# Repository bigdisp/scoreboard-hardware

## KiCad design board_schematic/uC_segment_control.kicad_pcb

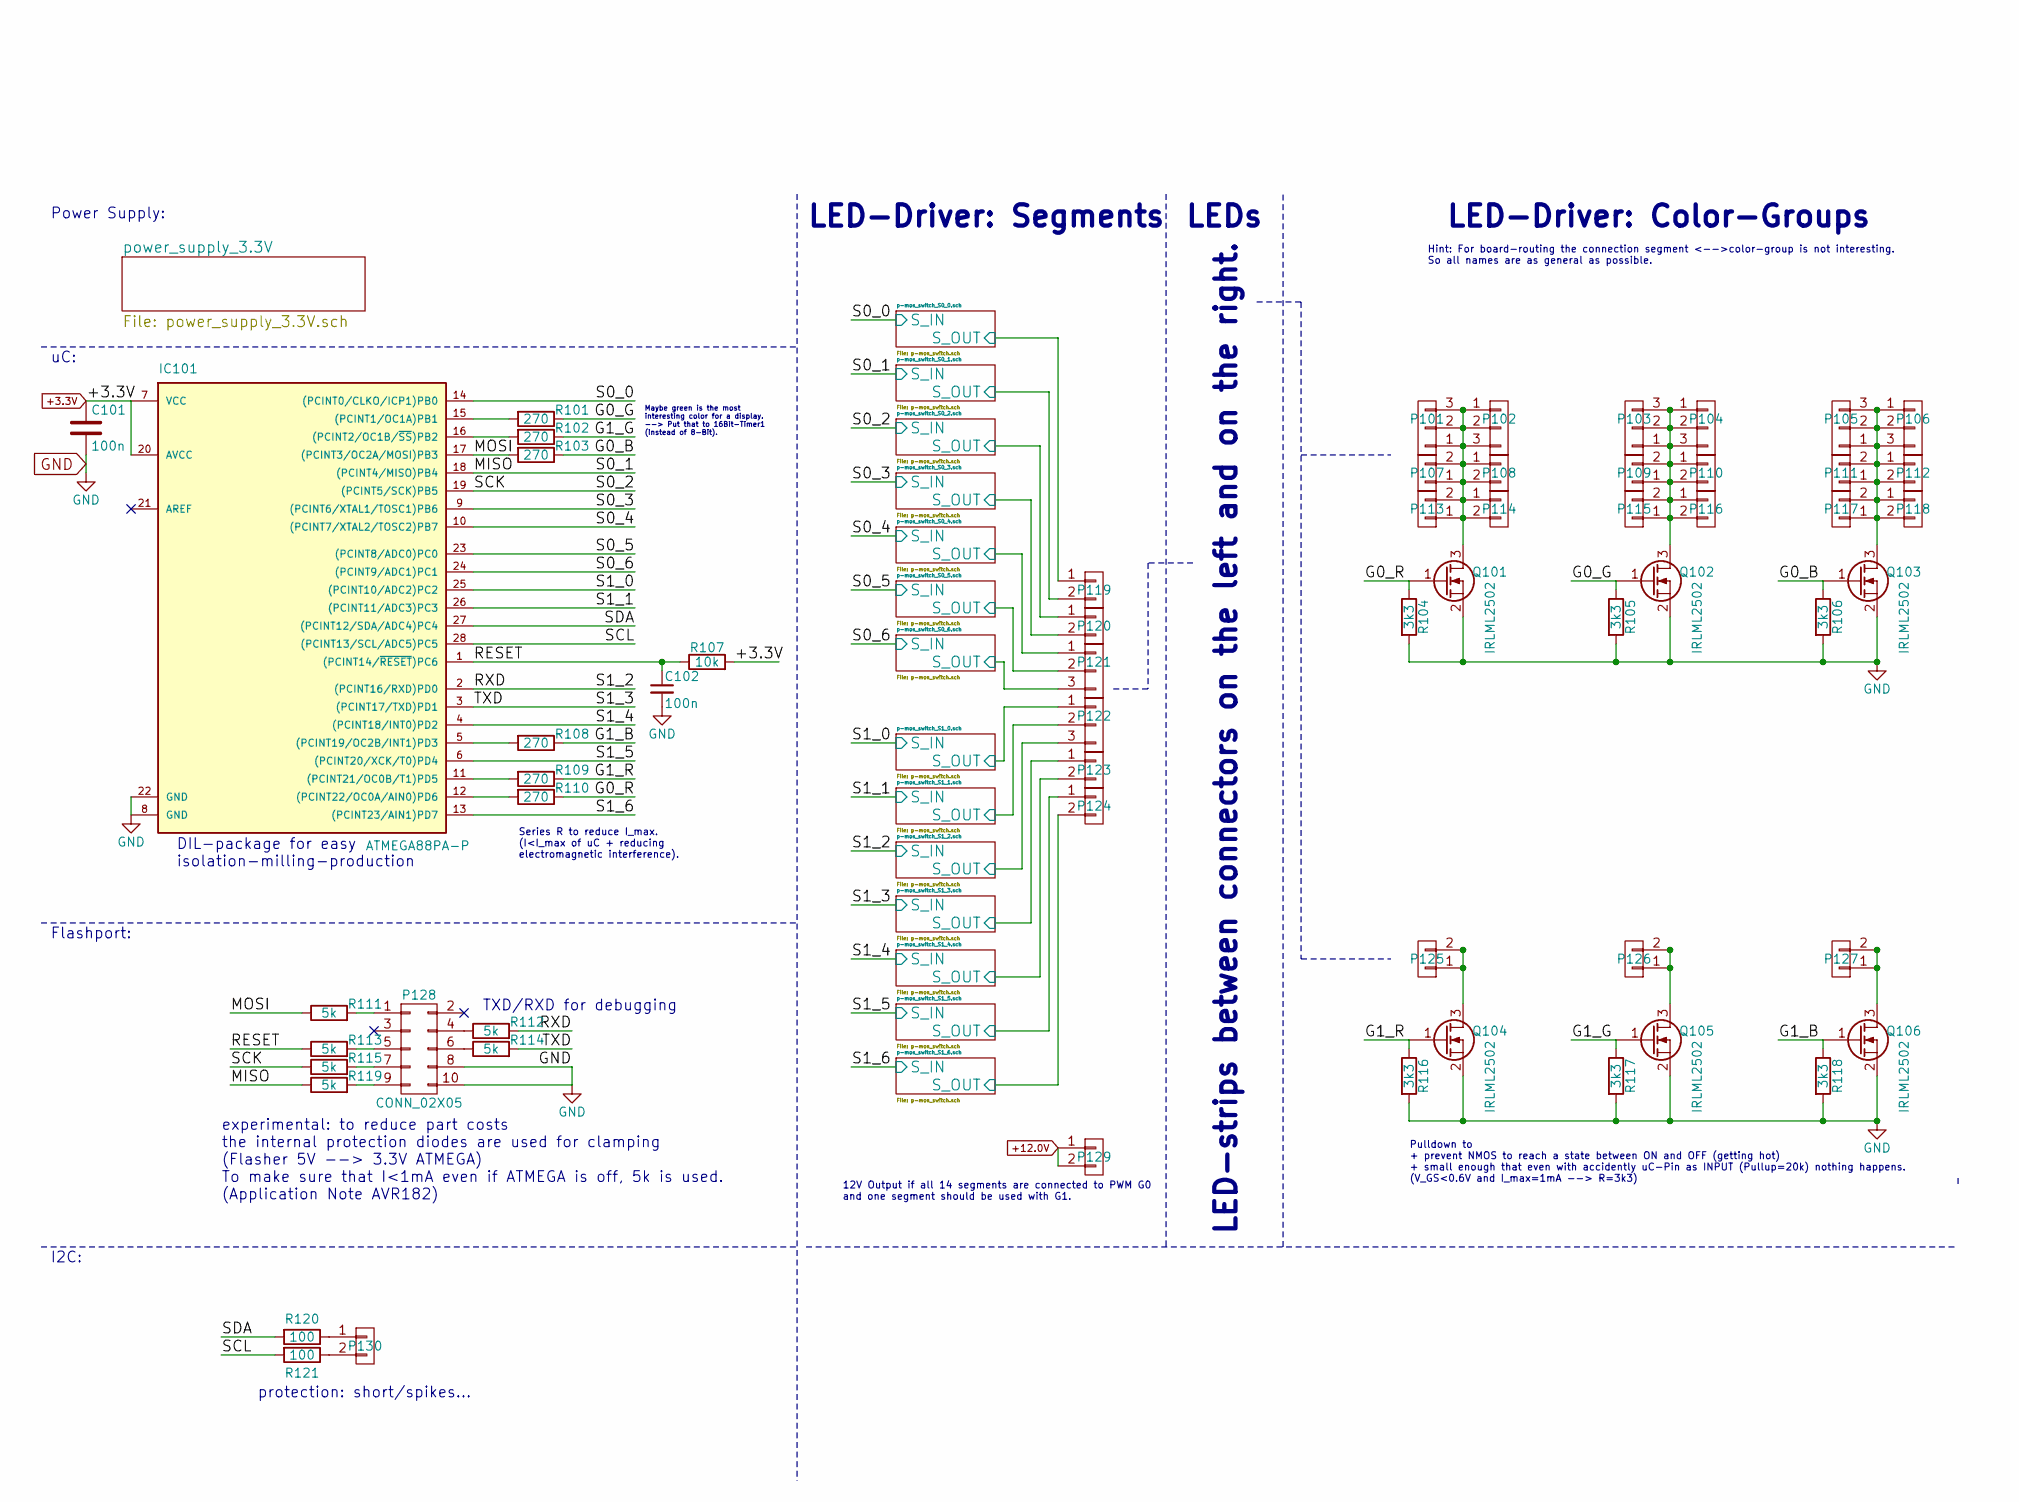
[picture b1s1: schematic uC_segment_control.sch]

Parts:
C101, C102: 100n; C_0805_HandSoldering
IC101: ATMEGA88PA-P; DIP-28_W7.62mm_LongPads
P101, P102, P103, P104, P105, P106, P121, P122: CONN_01X03; AK300-3
P107, P108, P109, P110, P111, P112, P113, P114, P115, P116, P117, P118, P119, P120, P123, P124, P125, P126, P127, P129, P130: CONN_01X02; AK300-2
P128: CONN_02X05; IDC_Header_Straight_10pins_0.6_clearance
Q101, Q102, Q103, Q104, Q105, Q106: IRLML2502; SOT-23_Handsoldering
R101, R102, R103, R108, R109, R110: 270; R_0805_HandSoldering
R104, R105, R106, R116, R117, R118: 3k3; R_0805_HandSoldering
R107: 10k; R_0805_HandSoldering
R111, R112, R113, R114, R115, R119: 5k; R_0805_HandSoldering
R120, R121: 100; R_0805_HandSoldering

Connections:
+3.3V: C101.1, IC101.7 (VCC), IC101.20 (AVCC), R107.2; also elsewhere on the board
+12.0V: P129.1, P129.2; also elsewhere on the board
/G0_B: Q103.1 (G), R103.1, R106.1
/G0_G: Q102.1 (G), R101.1, R105.1
/G0_R: Q101.1 (G), R104.1, R110.1
/G1_B: Q106.1 (G), R108.1, R118.1
/G1_G: Q105.1 (G), R102.1, R117.1
/G1_R: Q104.1 (G), R109.1, R116.1
/MOSI: IC101.17 ((PCINT3/OC2A/MOSI)PB3), R103.2, R111.1
/RESET: C102.1, IC101.1 ((PCINT14/~RESET~)PC6), R107.1, R113.1
/SCL: IC101.28 ((PCINT13/SCL/ADC5)PC5), R121.2
/SDA: IC101.27 ((PCINT12/SDA/ADC4)PC4), R120.2
/p-mos_switch_S0_0.sch/S_IN: IC101.14 ((PCINT0/CLKO/ICP1)PB0); also elsewhere on the board
/p-mos_switch_S0_0.sch/S_OUT: P119.1; also elsewhere on the board
/p-mos_switch_S0_1.sch/S_IN: IC101.18 ((PCINT4/MISO)PB4), R119.1; also elsewhere on the board
/p-mos_switch_S0_1.sch/S_OUT: P119.2; also elsewhere on the board
/p-mos_switch_S0_2.sch/S_IN: IC101.19 ((PCINT5/SCK)PB5), R115.1; also elsewhere on the board
/p-mos_switch_S0_2.sch/S_OUT: P120.1; also elsewhere on the board
/p-mos_switch_S0_3.sch/S_IN: IC101.9 ((PCINT6/XTAL1/TOSC1)PB6); also elsewhere on the board
/p-mos_switch_S0_3.sch/S_OUT: P120.2; also elsewhere on the board
/p-mos_switch_S0_4.sch/S_IN: IC101.10 ((PCINT7/XTAL2/TOSC2)PB7); also elsewhere on the board
/p-mos_switch_S0_4.sch/S_OUT: P121.1; also elsewhere on the board
/p-mos_switch_S0_5.sch/S_IN: IC101.23 ((PCINT8/ADC0)PC0); also elsewhere on the board
/p-mos_switch_S0_5.sch/S_OUT: P121.2; also elsewhere on the board
/p-mos_switch_S0_6.sch/S_IN: IC101.24 ((PCINT9/ADC1)PC1); also elsewhere on the board
/p-mos_switch_S0_6.sch/S_OUT: P121.3; also elsewhere on the board
/p-mos_switch_S1_0.sch/S_IN: IC101.25 ((PCINT10/ADC2)PC2); also elsewhere on the board
/p-mos_switch_S1_0.sch/S_OUT: P122.1; also elsewhere on the board
/p-mos_switch_S1_1.sch/S_IN: IC101.26 ((PCINT11/ADC3)PC3); also elsewhere on the board
/p-mos_switch_S1_1.sch/S_OUT: P122.2; also elsewhere on the board
/p-mos_switch_S1_2.sch/S_IN: IC101.2 ((PCINT16/RXD)PD0), R112.2; also elsewhere on the board
/p-mos_switch_S1_2.sch/S_OUT: P122.3; also elsewhere on the board
/p-mos_switch_S1_3.sch/S_IN: IC101.3 ((PCINT17/TXD)PD1), R114.2; also elsewhere on the board
/p-mos_switch_S1_3.sch/S_OUT: P123.1; also elsewhere on the board
/p-mos_switch_S1_4.sch/S_IN: IC101.4 ((PCINT18/INT0)PD2); also elsewhere on the board
/p-mos_switch_S1_4.sch/S_OUT: P123.2; also elsewhere on the board
/p-mos_switch_S1_5.sch/S_IN: IC101.6 ((PCINT20/XCK/T0)PD4); also elsewhere on the board
/p-mos_switch_S1_5.sch/S_OUT: P124.1; also elsewhere on the board
/p-mos_switch_S1_6.sch/S_IN: IC101.13 ((PCINT23/AIN1)PD7); also elsewhere on the board
/p-mos_switch_S1_6.sch/S_OUT: P124.2; also elsewhere on the board
GND: C101.2, C102.2, IC101.8 (GND), IC101.22 (GND), P128.8, P128.10, Q101.2 (S), Q102.2 (S), Q103.2 (S), Q104.2 (S), Q105.2 (S), Q106.2 (S), R104.2, R105.2, R106.2, R116.2, R117.2, R118.2; also elsewhere on the board
unnamed: IC101.5 ((PCINT19/OC2B/INT1)PD3), R108.2
unnamed: IC101.11 ((PCINT21/OC0B/T1)PD5), R109.2
unnamed: IC101.12 ((PCINT22/OC0A/AIN0)PD6), R110.2
unnamed: IC101.15 ((PCINT1/OC1A)PB1), R101.2
unnamed: IC101.16 ((PCINT2/OC1B/~SS~)PB2), R102.2
unnamed: P101.1, P101.2, P101.3, P102.1, P102.2, P102.3, P107.1, P107.2, P108.1, P108.2, P113.1, P113.2, P114.1, P114.2, Q101.3 (D)
unnamed: P103.1, P103.2, P103.3, P104.1, P104.2, P104.3, P109.1, P109.2, P110.1, P110.2, P115.1, P115.2, P116.1, P116.2, Q102.3 (D)
unnamed: P105.1, P105.2, P105.3, P106.1, P106.2, P106.3, P111.1, P111.2, P112.1, P112.2, P117.1, P117.2, P118.1, P118.2, Q103.3 (D)
unnamed: P125.1, P125.2, Q104.3 (D)
unnamed: P126.1, P126.2, Q105.3 (D)
unnamed: P127.1, P127.2, Q106.3 (D)
unnamed: P128.1, R111.2
unnamed: P128.4, R112.1
unnamed: P128.5, R113.2
unnamed: P128.6, R114.1
unnamed: P128.7, R115.2
unnamed: P128.9, R119.2
unnamed: P130.1, R120.1
unnamed: P130.2, R121.1

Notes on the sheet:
DIL-package for easy isolation-milling-production
experimental: to reduce part costs the internal protection diodes are used for clamping (Flasher 5V --> 3.3V ATMEGA) To make sure that I<1mA even if ATMEGA is off, 5k is used. (Application Note AVR182)
Power Supply:
uC:
Flashport:
LED-Driver: Segments
LED-Driver: Color-Groups
Hint: For board-routing the connection segment <-->color-group is not interesting. So all names are as general as possible.
LED-strips between connectors on the left and on the right.
LEDs
Series R to reduce I_max. (I<I_max of uC + reducing electromagnetic interference).
Maybe green is the most interesting color for a display. --> Put that to 16Bit-Timer1 (instead of 8-Bit).
Pulldown to + prevent NMOS to reach a state between ON and OFF (getting hot) + small enough that even with accidently uC-Pin as INPUT (Pullup=20k) nothing happens. (V_GS<0.6V and I_max=1mA --> R=3k3)
TXD/RXD for debugging
I2C:
protection: short/spikes...
12V Output if all 14 segments are connected to PWM G0 and one segment should be used with G1.

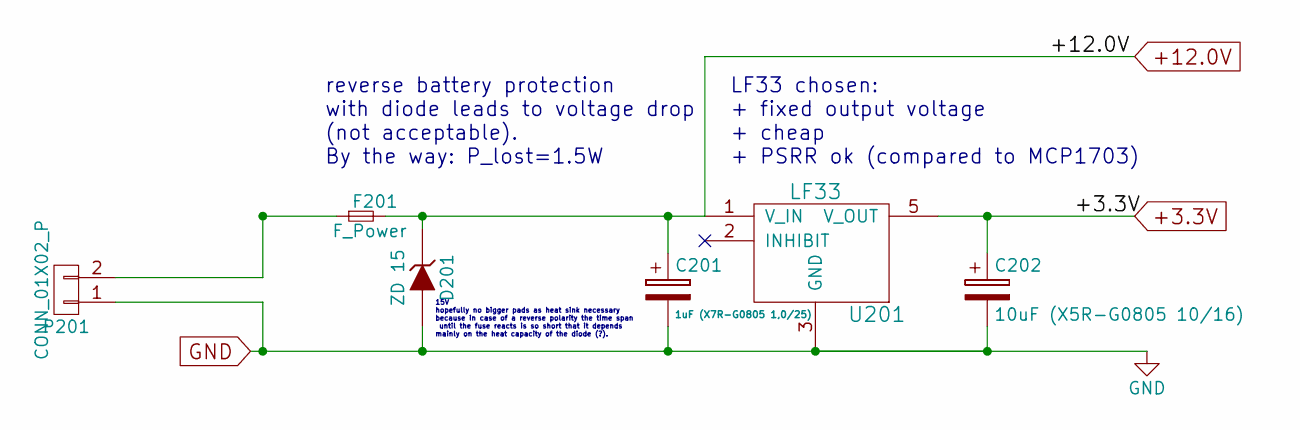
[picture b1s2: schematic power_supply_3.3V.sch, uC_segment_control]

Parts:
C201: 1uF (X7R-G0805 1,0/25); C_0805_HandSoldering
C202: 10uF (X5R-G0805 10/16); C_0805_HandSoldering
D201: ZD 15; Diode_DO-41_SOD81_Horizontal_RM10
F201: F_Power; Fuseholder5x20_horiz_SemiClosed_Casing10x25mm
P201: CONN_01X02_P; AK300-2
U201: LF33; D-PAK

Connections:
+3.3V: C202.1, U201.5 (V_OUT); also elsewhere on the board
+12.0V: C201.1, D201.1 (K), F201.2, U201.1 (V_IN); also elsewhere on the board
GND: C201.2, C202.2, D201.2 (A), P201.1, U201.3 (GND); also elsewhere on the board
unnamed: F201.1, P201.2

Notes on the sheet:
LF33 chosen: + fixed output voltage + cheap + PSRR ok (compared to MCP1703)
reverse battery protection with diode leads to voltage drop (not acceptable). By the way: P_lost=1.5W
15V hopefully no bigger pads as heat sink necessary because in case of a reverse polarity the time span until the fuse reacts is so short that it depends mainly on the heat capacity of the diode (?).

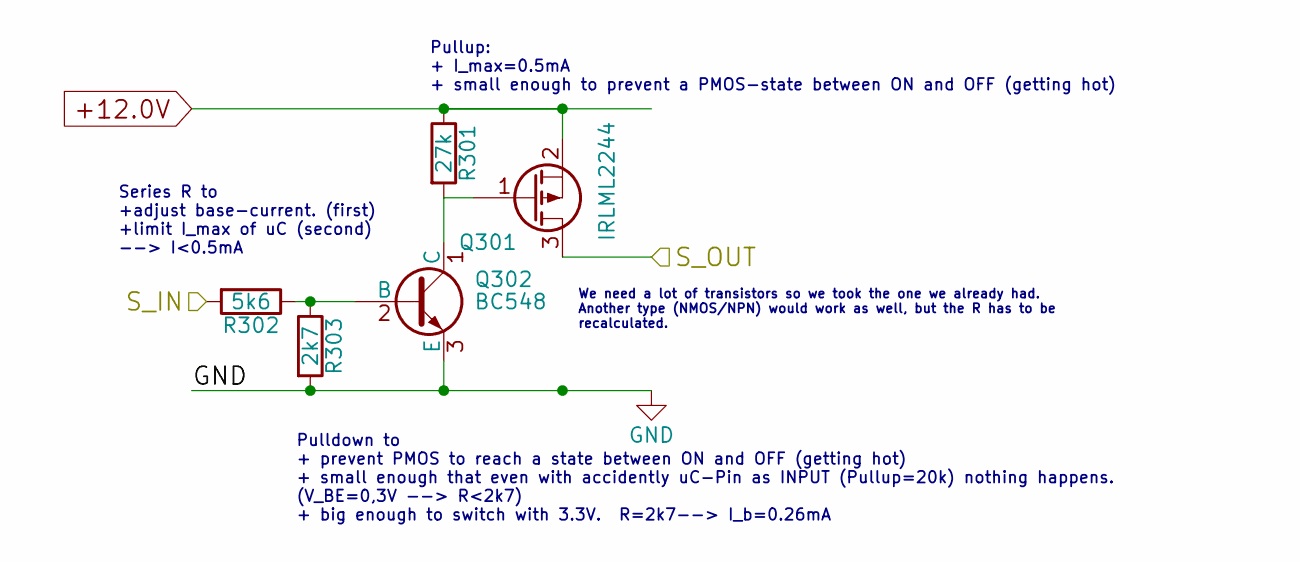
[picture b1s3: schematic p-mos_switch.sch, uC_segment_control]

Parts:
Q301: IRLML2244; SOT-23_Handsoldering
Q302: BC548; TO-92_Molded_0.6space_Oval
R301: 27k; R_0805_HandSoldering
R302: 5k6; R_0805_HandSoldering
R303: 2k7; R_0805_HandSoldering

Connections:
+12.0V: Q301.2 (S), R301.1; also elsewhere on the board
/p-mos_switch_S0_0.sch/S_IN: R302.2; also elsewhere on the board
/p-mos_switch_S0_0.sch/S_OUT: Q301.3 (D); also elsewhere on the board
GND: Q302.3 (E), R303.2; also elsewhere on the board
unnamed: Q301.1 (G), Q302.1 (C), R301.2
unnamed: Q302.2 (B), R302.1, R303.1

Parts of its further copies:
Q401, Q501, Q601, Q701, Q801, Q901, Q1001, Q1101, Q1201, Q1301, Q1401, Q1501, Q1601: IRLML2244; SOT-23_Handsoldering
Q402, Q502, Q602, Q702, Q802, Q902, Q1002, Q1102, Q1202, Q1302, Q1402, Q1502, Q1602: BC548; TO-92_Molded_0.6space_Oval
R401, R501, R601, R701, R801, R901, R1001, R1101, R1201, R1301, R1401, R1501, R1601: 27k; R_0805_HandSoldering
R402, R502, R602, R702, R802, R902, R1002, R1102, R1202, R1302, R1402, R1502, R1602: 5k6; R_0805_HandSoldering
R403, R503, R603, R703, R803, R903, R1003, R1103, R1203, R1303, R1403, R1503, R1603: 2k7; R_0805_HandSoldering

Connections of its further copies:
+12.0V: Q401.2 (S), Q501.2 (S), Q601.2 (S), Q701.2 (S), Q801.2 (S), Q901.2 (S), Q1001.2 (S), Q1101.2 (S), Q1201.2 (S), Q1301.2 (S), Q1401.2 (S), Q1501.2 (S), Q1601.2 (S), R401.1, R501.1, R601.1, R701.1, R801.1, R901.1, R1001.1, R1101.1, R1201.1, R1301.1, R1401.1, R1501.1, R1601.1; also elsewhere on the board
/p-mos_switch_S0_1.sch/S_IN: R402.2; also elsewhere on the board
/p-mos_switch_S0_1.sch/S_OUT: Q401.3 (D); also elsewhere on the board
/p-mos_switch_S0_2.sch/S_IN: R502.2; also elsewhere on the board
/p-mos_switch_S0_2.sch/S_OUT: Q501.3 (D); also elsewhere on the board
/p-mos_switch_S0_3.sch/S_IN: R602.2; also elsewhere on the board
/p-mos_switch_S0_3.sch/S_OUT: Q601.3 (D); also elsewhere on the board
/p-mos_switch_S0_4.sch/S_IN: R702.2; also elsewhere on the board
/p-mos_switch_S0_4.sch/S_OUT: Q701.3 (D); also elsewhere on the board
/p-mos_switch_S0_5.sch/S_IN: R802.2; also elsewhere on the board
/p-mos_switch_S0_5.sch/S_OUT: Q801.3 (D); also elsewhere on the board
/p-mos_switch_S0_6.sch/S_IN: R902.2; also elsewhere on the board
/p-mos_switch_S0_6.sch/S_OUT: Q901.3 (D); also elsewhere on the board
/p-mos_switch_S1_0.sch/S_IN: R1002.2; also elsewhere on the board
/p-mos_switch_S1_0.sch/S_OUT: Q1001.3 (D); also elsewhere on the board
/p-mos_switch_S1_1.sch/S_IN: R1102.2; also elsewhere on the board
/p-mos_switch_S1_1.sch/S_OUT: Q1101.3 (D); also elsewhere on the board
/p-mos_switch_S1_2.sch/S_IN: R1202.2; also elsewhere on the board
/p-mos_switch_S1_2.sch/S_OUT: Q1201.3 (D); also elsewhere on the board
/p-mos_switch_S1_3.sch/S_IN: R1302.2; also elsewhere on the board
/p-mos_switch_S1_3.sch/S_OUT: Q1301.3 (D); also elsewhere on the board
/p-mos_switch_S1_4.sch/S_IN: R1402.2; also elsewhere on the board
/p-mos_switch_S1_4.sch/S_OUT: Q1401.3 (D); also elsewhere on the board
/p-mos_switch_S1_5.sch/S_IN: R1502.2; also elsewhere on the board
/p-mos_switch_S1_5.sch/S_OUT: Q1501.3 (D); also elsewhere on the board
/p-mos_switch_S1_6.sch/S_IN: R1602.2; also elsewhere on the board
/p-mos_switch_S1_6.sch/S_OUT: Q1601.3 (D); also elsewhere on the board
GND: Q402.3 (E), Q502.3 (E), Q602.3 (E), Q702.3 (E), Q802.3 (E), Q902.3 (E), Q1002.3 (E), Q1102.3 (E), Q1202.3 (E), Q1302.3 (E), Q1402.3 (E), Q1502.3 (E), Q1602.3 (E), R403.2, R503.2, R603.2, R703.2, R803.2, R903.2, R1003.2, R1103.2, R1203.2, R1303.2, R1403.2, R1503.2, R1603.2; also elsewhere on the board
unnamed: Q401.1 (G), Q402.1 (C), R401.2
unnamed: Q402.2 (B), R402.1, R403.1
unnamed: Q501.1 (G), Q502.1 (C), R501.2
unnamed: Q502.2 (B), R502.1, R503.1
unnamed: Q601.1 (G), Q602.1 (C), R601.2
unnamed: Q602.2 (B), R602.1, R603.1
unnamed: Q701.1 (G), Q702.1 (C), R701.2
unnamed: Q702.2 (B), R702.1, R703.1
unnamed: Q801.1 (G), Q802.1 (C), R801.2
unnamed: Q802.2 (B), R802.1, R803.1
unnamed: Q901.1 (G), Q902.1 (C), R901.2
unnamed: Q902.2 (B), R902.1, R903.1
unnamed: Q1001.1 (G), Q1002.1 (C), R1001.2
unnamed: Q1002.2 (B), R1002.1, R1003.1
unnamed: Q1101.1 (G), Q1102.1 (C), R1101.2
unnamed: Q1102.2 (B), R1102.1, R1103.1
unnamed: Q1201.1 (G), Q1202.1 (C), R1201.2
unnamed: Q1202.2 (B), R1202.1, R1203.1
unnamed: Q1301.1 (G), Q1302.1 (C), R1301.2
unnamed: Q1302.2 (B), R1302.1, R1303.1
unnamed: Q1401.1 (G), Q1402.1 (C), R1401.2
unnamed: Q1402.2 (B), R1402.1, R1403.1
unnamed: Q1501.1 (G), Q1502.1 (C), R1501.2
unnamed: Q1502.2 (B), R1502.1, R1503.1
unnamed: Q1601.1 (G), Q1602.1 (C), R1601.2
unnamed: Q1602.2 (B), R1602.1, R1603.1

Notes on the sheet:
Pulldown to + prevent PMOS to reach a state between ON and OFF (getting hot) + small enough that even with accidently uC-Pin as INPUT (Pullup=20k) nothing happens. (V_BE=0,3V --> R<2k7) + big enough to switch with 3.3V. R=2k7--> I_b=0.26mA
We need a lot of transistors so we took the one we already had. Another type (NMOS/NPN) would work as well, but the R has to be recalculated.
Series R to +adjust base-current. (first) +limit I_max of uC (second) --> I<0.5mA
Pullup: + I_max=0.5mA + small enough to prevent a PMOS-state between ON and OFF (getting hot)

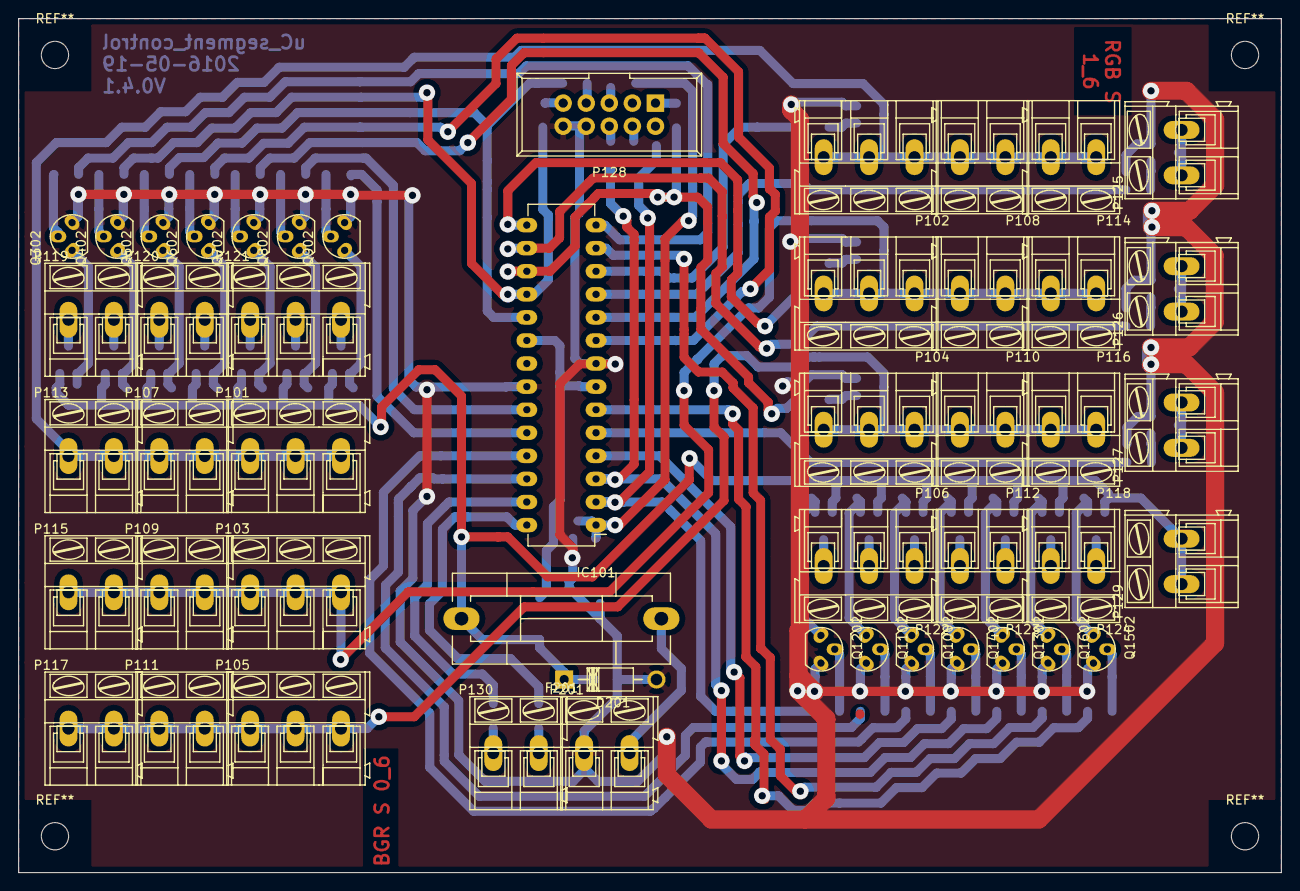
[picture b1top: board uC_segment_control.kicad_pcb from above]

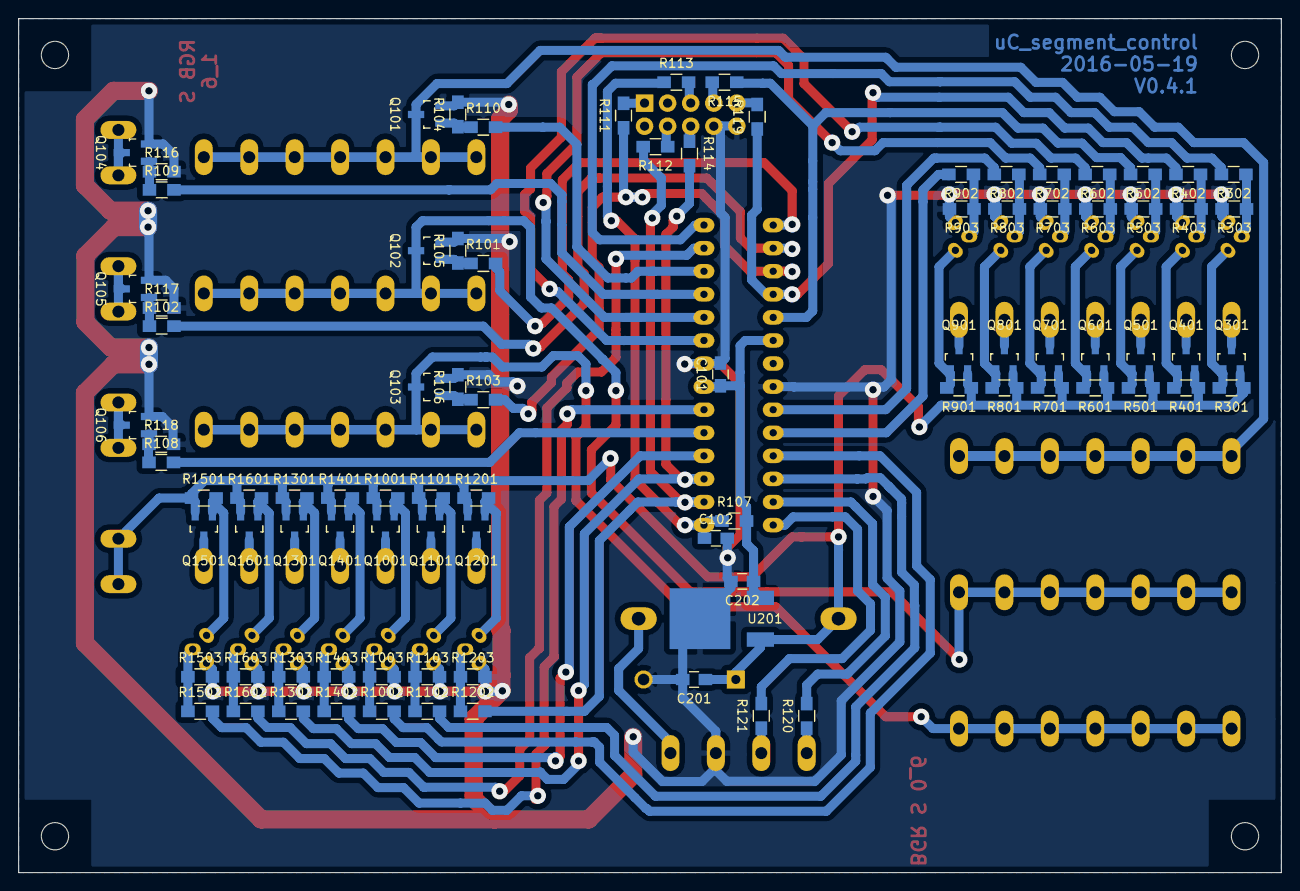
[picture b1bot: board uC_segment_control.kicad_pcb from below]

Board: 2 copper layers, 139.0 x 94.0 mm, 136 parts (88 on the bottom side), 89 nets.

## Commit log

2016-05-01 Readme
2016-05-01 License
2016-05-01 test
2016-05-04 V0.1.1
2016-05-05 V0.2.1: First schematic for BOM
2016-05-12 V0.3.1: First layout
2016-05-19 V0.4.1 bigger pads footprint flashport for better milling. Case added.
